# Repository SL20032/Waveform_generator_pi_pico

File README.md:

# Waveform_generator_pi_pico

## Experimental: project in active development
Do not use 
## Basic Information
Projest aims to build simple waveform generator (with digitaly adjustable amplitude and offset of signal) based around AD9833 DDS chip controled via PC app. With digital and comunication part of the circutry beeing handled by RP2040 on Pi Pico board. 

## Hardware
hardware part of this projest consst of two main elements:
### Analog
Responsible for generating (AD9833) and ampifaing and offsetting (pair of LM7171) analog signal. As well as aditional components needed for example for square wave processing. (attached baord layout require redesign for proper operation of offset capability - work in progress)

### Digital
Responsible for controling analog part of circutry using digital potenciometers (MCP4231 / MC4251) integrated on analog board prototype as well as comunication with PC using galvanicly isoleded interfece.
## PC Software
Coming soon

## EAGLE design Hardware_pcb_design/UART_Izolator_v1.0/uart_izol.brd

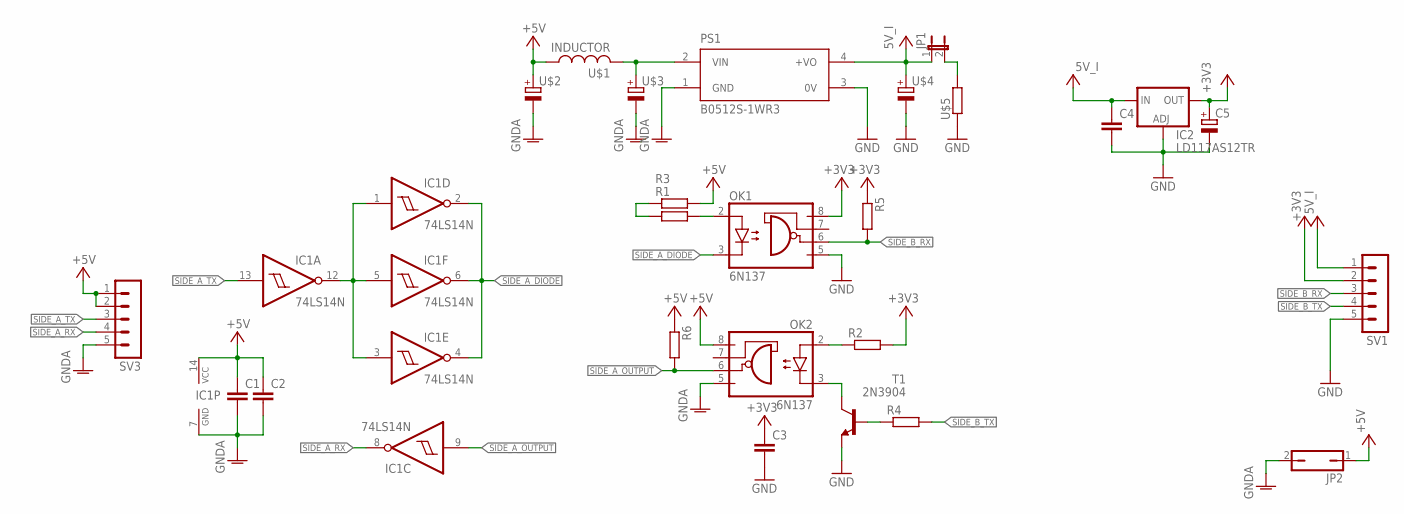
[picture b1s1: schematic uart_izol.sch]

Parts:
C1, C2, C3, C4: C-EUC0805; C0805
C5: CPOL-EUSMCB; SMC_B
IC1: 74LS14N; DIL14
IC2: LD117AS12TR; SOT223
JP1: JP1E; JP1
JP2: JP1Q; JP1
OK1, OK2: 6N137; DIL08
PS1: B0512S-1WR3; CONV_B0512S-1WR3
R1, R2, R3, R4, R5, R6: R-EU_M0805; M0805
SV1, SV3: MA05-1
T1: 2N3904; TO92
U$1: INDUCTOR; 0207/10
U$2, U$3, U$4: CAPACITOR; E2,5-7
U$5: RESISTOR; 0207/10

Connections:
+3V3: C3.1, C5.+, IC2.4 (OUT), OK1.8 (VCC), R2.2, R5.1, SV1.2
+5V: C1.1, C2.1, IC1.14 (VCC), JP2.1, OK2.8 (VCC), R3.2, R6.1, SV3.1, SV3.2, U$1.1, U$2.+
GND: C3.2, C4.2, C5.-, IC2.1 (ADJ), OK1.5 (GND), PS1.3 (0V), SV1.5, T1.3 (E), U$4.-, U$5.1
GNDA: C1.2, C2.2, IC1.7 (GND), JP2.2, OK2.5 (GND), PS1.1 (GND), SV3.5, U$2.-, U$3.-
unnamed: OK1.2 (A), R1.2
unnamed: OK2.2 (A), R2.1
unnamed: R1.1, R3.1
unnamed: OK2.3 (C), T1.1 (C)
unnamed: JP1.2, U$5.2
unnamed: R4.1, T1.2 (B)
unnamed: PS1.2 (VIN), U$1.2, U$3.+
unnamed: IC1.1 (I), IC1.3 (I), IC1.5 (I), IC1.12 (O)
SIDE_A_DIODE: IC1.2 (O), IC1.4 (O), IC1.6 (O), OK1.3 (C)
SIDE_A_OUTPUT: IC1.9 (I), OK2.6 (VO), R6.2
SIDE_A_RX: IC1.8 (O), SV3.4
SIDE_A_TX: IC1.13 (I), SV3.3
SIDE_B_RX: OK1.6 (VO), R5.2, SV1.3
SIDE_B_TX: R4.2, SV1.4
VCC: C4.1, IC2.3 (IN), JP1.1, PS1.4 (+VO), SV1.1, U$4.+

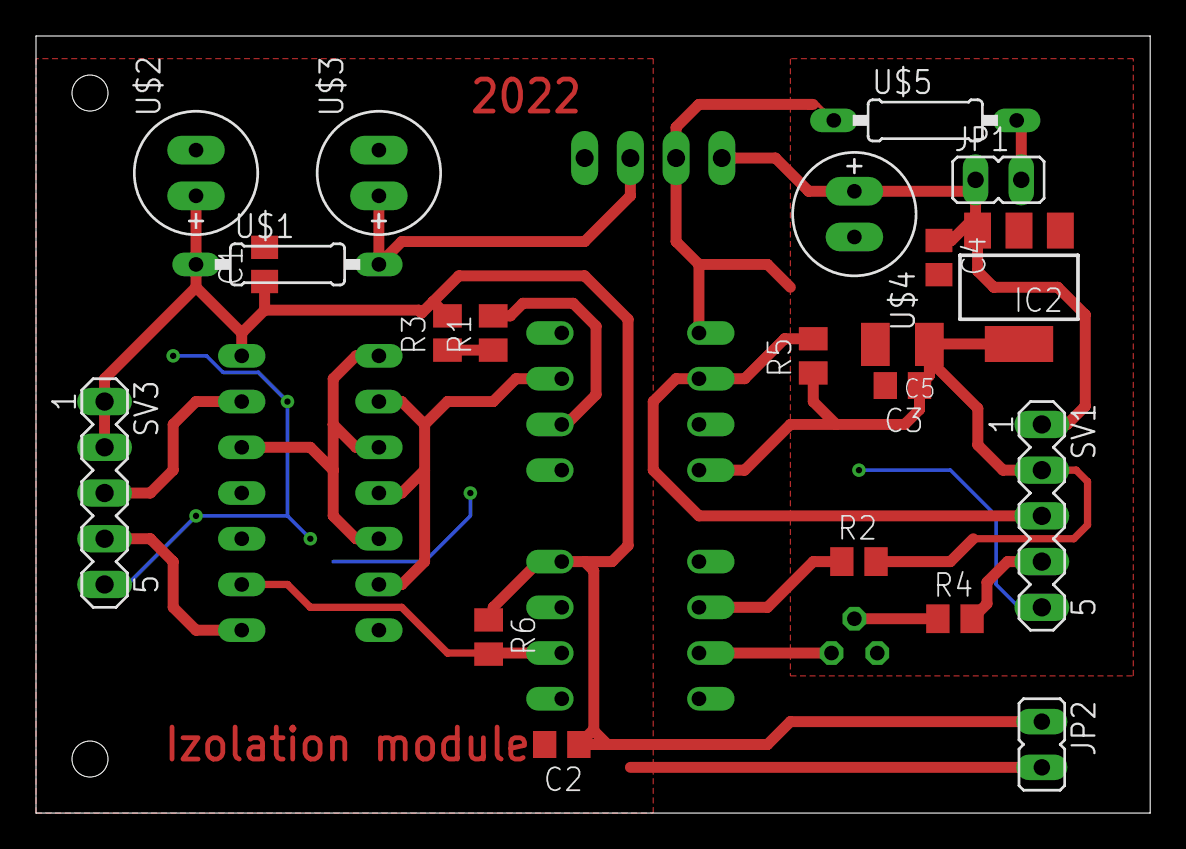
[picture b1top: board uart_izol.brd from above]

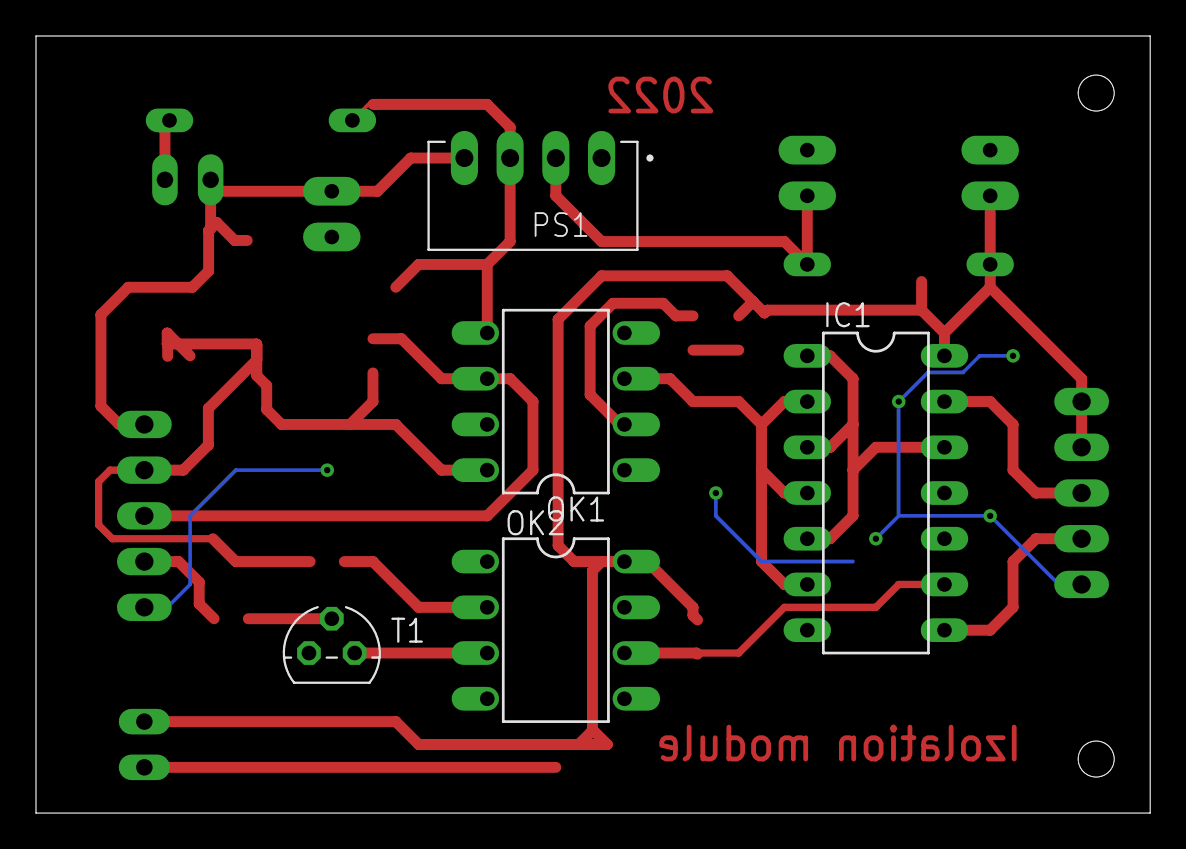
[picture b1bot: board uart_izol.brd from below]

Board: 2 copper layers, 61.9 x 43.2 mm, 26 parts (5 on the bottom side), 19 nets.

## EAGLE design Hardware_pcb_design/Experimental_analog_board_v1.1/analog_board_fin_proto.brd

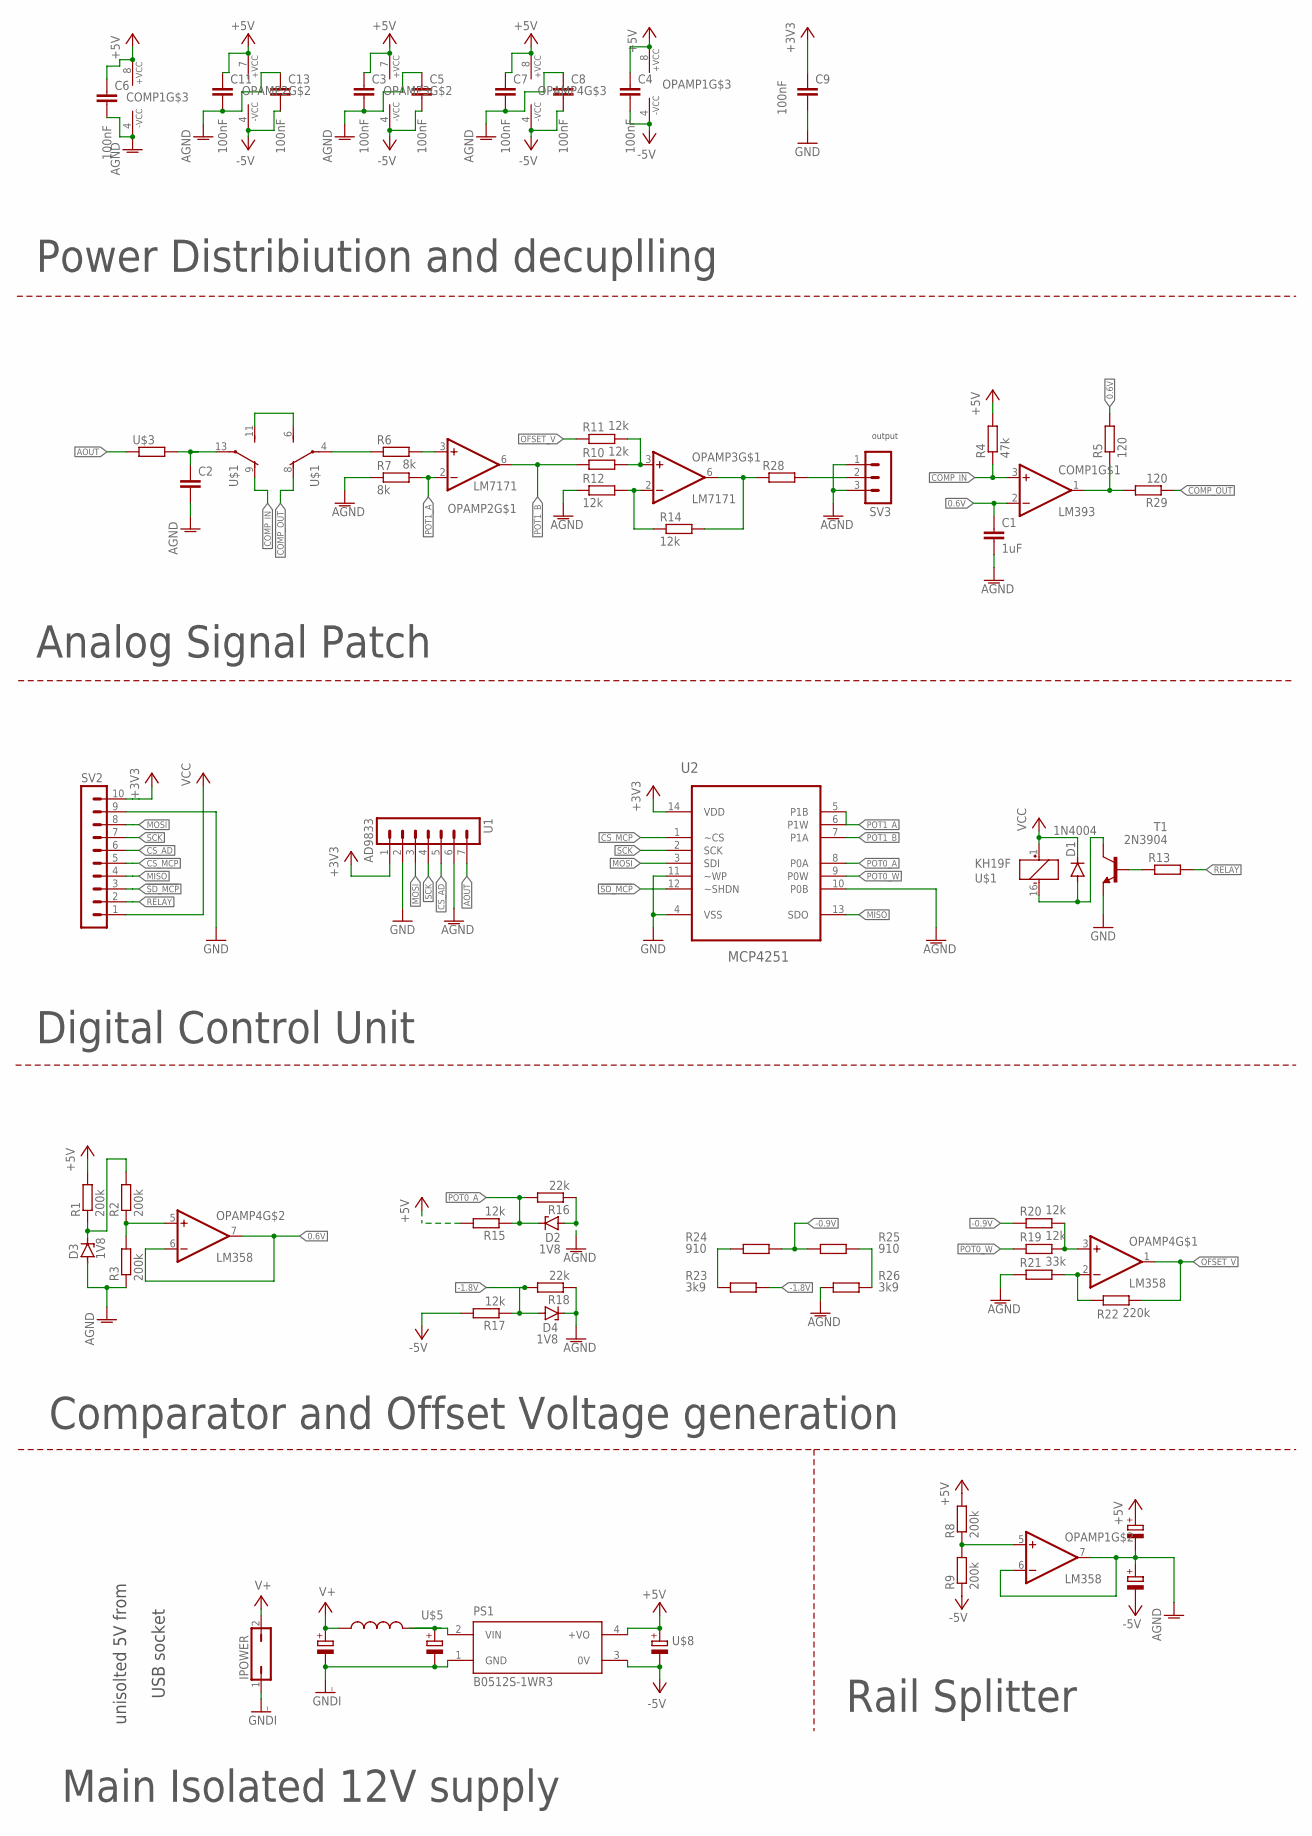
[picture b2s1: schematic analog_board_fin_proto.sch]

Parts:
C1: 1uF; C0805
C2: C-EU025-025X050; C025-025X050
C3, C4, C5, C6, C7, C8, C9, C11, C13: 100nF; C0805
COMP1: LM393; DIL08
D1: 1N4004; DO41-10
D2, D3, D4: 1V8; SOD80C
IPOWER: POT; JP1
OPAMP1, OPAMP4: LM358; DIL08
OPAMP2, OPAMP3: LM7171; DIL08
PS1: B0512S-1WR3; CONV_B0512S-1WR3
R1, R2, R3, R8, R9: 200k; R0805
R4: 47k; R0805
R5, R29: 120; R0805
R6, R7: 8k; R0805
R10, R11, R12, R14, R15, R17, R19, R20: 12k; R0805
R13: R-EU_R0805; R0805
R16, R18: 22k; R0805
R21: 33k; R0805
R22: 220k; R0805
R23, R26: 3k9; R0805
R24, R25: 910; R0805
R28: R-EU_R2512; R2512
SV2: MA10-1
SV3: MA03-1
T1: 2N3904; TO92
U1: AD9833; MA07-1
U2: MCP4251; DIL14
U$1: KH19F; BT-XX-S
U$3: RESISTOR; 0207/10
U$5, U$8, U$9, U$10: CAPACITOR; E2,5-7
U$6: 100nF; E2,5-7
U$7: INDUCTOR; 0207/10

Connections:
0.6V: C1.1, COMP1.2 (-IN), OPAMP4.6 (-IN), OPAMP4.7 (OUT), R5.2
!SD_MCP: SV2.3, U2.12 (~SHDN)
+3V3: C9.1, SV2.10, U1.1, U2.14 (VDD)
+5V: C3.1, C4.1, C6.1, C7.1, C11.1, COMP1.8 (VCC), OPAMP1.8 (VCC), OPAMP2.7 (VCC), OPAMP3.7 (VCC), OPAMP4.8 (VCC), PS1.4 (+VO), R1.2, R4.2, R8.2, R15.2, U$8.+, U$9.+
-0.9V: R20.1, R24.1, R25.2
-1.8V: D4.A, R17.1, R18.2, R23.2
-5V: C4.2, C5.2, C8.2, C13.2, OPAMP1.4 (GND), OPAMP2.4 (GND), OPAMP3.4 (GND), OPAMP4.4 (GND), PS1.3 (0V), R9.1, R17.2, U$8.-, U$10.-
AGND: C1.2, C2.2, C3.2, C5.1, C6.2, C7.2, C8.1, C11.2, C13.1, COMP1.4 (GND), D2.A, D3.A, D4.C, OPAMP1.6 (-IN), OPAMP1.7 (OUT), R3.1, R7.1, R12.1, R16.1, R18.1, R21.1, R26.1, SV3.1, SV3.3, U1.6, U2.10 (P0B), U$9.-, U$10.+
AOUT: U1.7, U$3.1
COMP_IN: COMP1.3 (+IN), R4.1, U$1.9 (O)
COMP_OUT: R29.1, U$1.8 (O)
CS_AD: SV2.6, U1.5
CS_MCP: SV2.5, U2.1 (~CS)
GND: C9.2, SV2.9, T1.3 (E), U1.2, U2.4 (VSS), U2.11 (~WP)
GNDI: IPOWER.1, PS1.1 (GND), U$5.-, U$6.-
MISO: SV2.4, U2.13 (SDO)
MOSI: SV2.8, U1.3, U2.3 (SDI)
unnamed: OPAMP4.5 (+IN), R2.1, R3.2
unnamed: U$1.6 (S), U$1.11 (S)
unnamed: C2.1, U$1.13, U$3.2
unnamed: D3.C, R1.1, R2.2
unnamed: OPAMP3.3 (+IN), R10.2, R11.2
unnamed: R6.1, U$1.4
unnamed: OPAMP3.6 (OUT), R14.2, R28.1
unnamed: OPAMP3.2 (-IN), R12.2, R14.1
unnamed: OPAMP1.5 (+IN), R8.1, R9.2
unnamed: OPAMP4.3 (+IN), R19.2, R20.2
unnamed: R28.2, SV3.2
unnamed: OPAMP2.3 (+IN), R6.2
unnamed: R23.1, R24.2
unnamed: OPAMP4.2 (-IN), R21.2, R22.1
unnamed: R25.1, R26.2
unnamed: PS1.2 (VIN), U$5.+, U$7.2
unnamed: D1.A, T1.1 (C), U$1.16 (-)
unnamed: COMP1.1 (OUT), R5.1, R29.2
unnamed: R13.1, T1.2 (B)
OFSET_V: OPAMP4.1 (OUT), R11.1, R22.2
POT0_A: D2.C, R15.1, R16.2, U2.8 (P0A)
POT0_W: R19.1, U2.9 (P0W)
POT1_A: OPAMP2.2 (-IN), R7.2, U2.5 (P1B), U2.6 (P1W)
POT1_B: OPAMP2.6 (OUT), R10.1, U2.7 (P1A)
RELAY: R13.2, SV2.2
SCK: SV2.7, U1.4, U2.2 (SCK)
V+: IPOWER.2, U$6.+, U$7.1
VCC: D1.C, SV2.1, U$1.1 (+)

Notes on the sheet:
unisolted 5V from
USB socket
Main Isolated 12V supply
Rail Splitter
Comparator and Offset Voltage generation
output
Digital Control Unit
Analog Signal Patch
Power Distribiution and decuplling

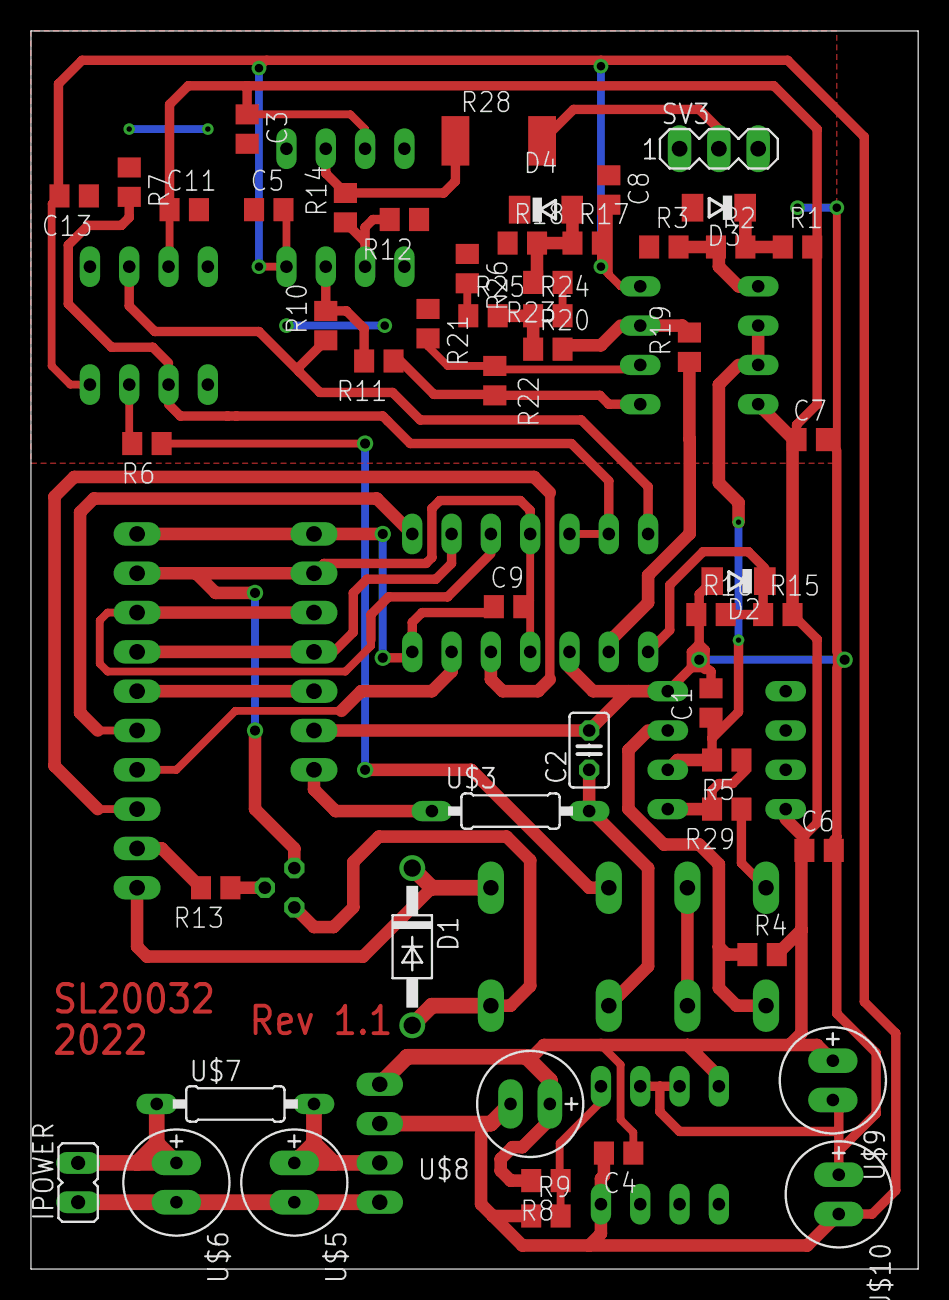
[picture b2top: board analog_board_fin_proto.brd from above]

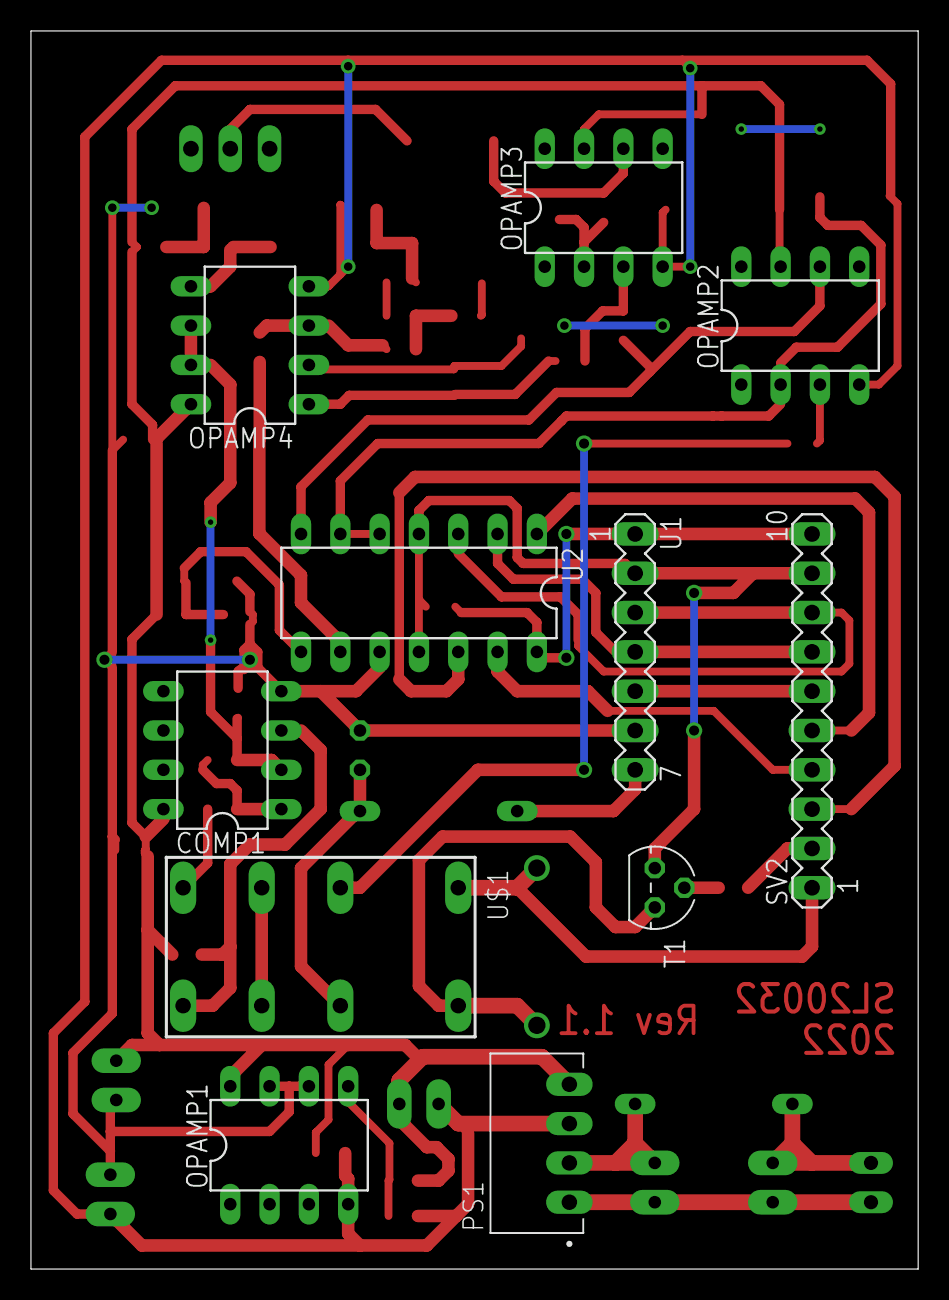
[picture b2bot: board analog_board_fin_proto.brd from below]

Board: 2 copper layers, 57.3 x 80.0 mm, 63 parts (11 on the bottom side), 45 nets.

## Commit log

2022-07-10 first commit (#01)
2022-07-10 Add DMA driven SPI Interface (#2)
2022-07-10 Implement AD9833 Driver (#3)
2022-07-12 Add simple PWM driver (#4)
2022-09-14 ADD MCP4231/4251 support + prototype integration
2022-09-14 Add Experimental Analog PCB and read me
2022-09-14 Readme picture update
2022-09-15 Create LICENSE
2022-09-16 Implementation of UART interfrce via DMA
2022-09-16 Implementation of UART interfrce via DMA 2
2022-09-16 UART Integration
2022-09-19 Transmision bug fixes
2022-10-16 Add USAR izolator PCB files
